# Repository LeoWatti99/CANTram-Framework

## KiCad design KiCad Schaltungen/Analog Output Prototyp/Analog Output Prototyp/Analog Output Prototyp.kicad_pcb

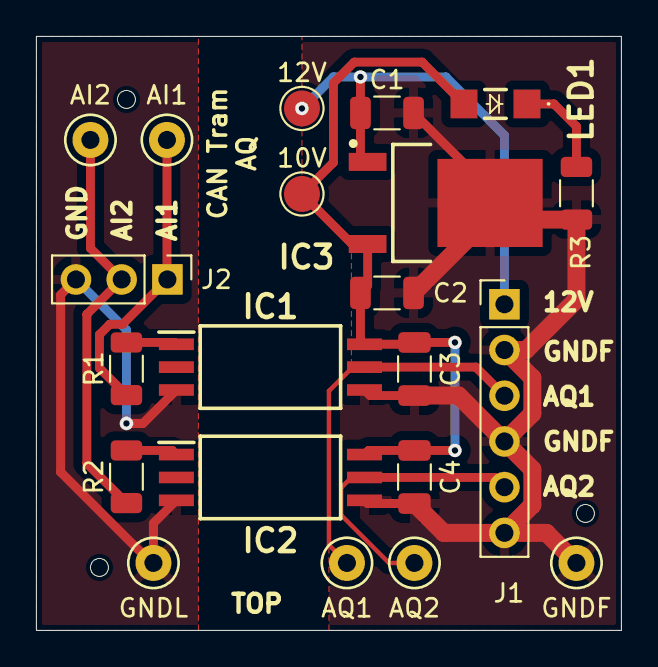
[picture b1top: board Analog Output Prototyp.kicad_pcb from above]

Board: 2 copper layers, 32.5 x 33.0 mm, 21 parts (0 on the bottom side), 11 nets.

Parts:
10V, 12V: TestPoint; TestPoint_Pad_D2.0mm
AI1, AI2: TestPoint_Probe; TestPoint_Keystone_5000-5004_Miniature
AQ1, AQ2: TestPoint_Probe; TestPoint_Keystone_5000-5004_Miniature
C1: 330n; C_1206_3216Metric
C2, C3, C4: 100n; C_1206_3216Metric
GNDF: TestPoint_Probe; TestPoint_Keystone_5000-5004_Miniature
GNDL: TestPoint_Probe; TestPoint_Keystone_5000-5004_Miniature
IC1, IC2: SI8261BAD-C-ISR; SOIC127P1150X265-6N
IC3: L78M10ABDT-TR; TO228P972X240-3N
J1: Conn_01x06; PinHeader_1x06_P2.54mm_Vertical
J2: Conn_01x03; PinHeader_1x03_P2.54mm_Vertical
LED1: 156120GS75000
R1, R2: 100; R_1206_3216Metric
R3: 6,2k; R_1206_3216Metric

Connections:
+10V: 10V.1, C2.1, C3.2, C4.2, IC1.6 (VDD), IC2.6 (VDD), IC3.3 (OUTPUT), LED1.2 (A)
+12V: 12V.1, C1.1, IC3.1 (INPUT), J1.1
GNDF: C1.2, C2.2, C3.1, C4.1, GNDF.1, IC1.4 (GND), IC2.4 (GND), IC3.4 (GND_(TAB)), J1.2, J1.4, J1.6, R3.2
GNDL: GNDL.1, IC1.3 (CATHODE), IC2.3 (CATHODE), J2.3
unnamed: IC1.1 (ANODE), R1.2
unnamed: AQ1.1, IC1.5 (VO), J1.3
unnamed: IC2.1 (ANODE), R2.2
unnamed: AQ2.1, IC2.5 (VO), J1.5
unnamed: AI1.1, J2.1, R1.1
unnamed: AI2.1, J2.2, R2.1
unnamed: LED1.1 (K), R3.1

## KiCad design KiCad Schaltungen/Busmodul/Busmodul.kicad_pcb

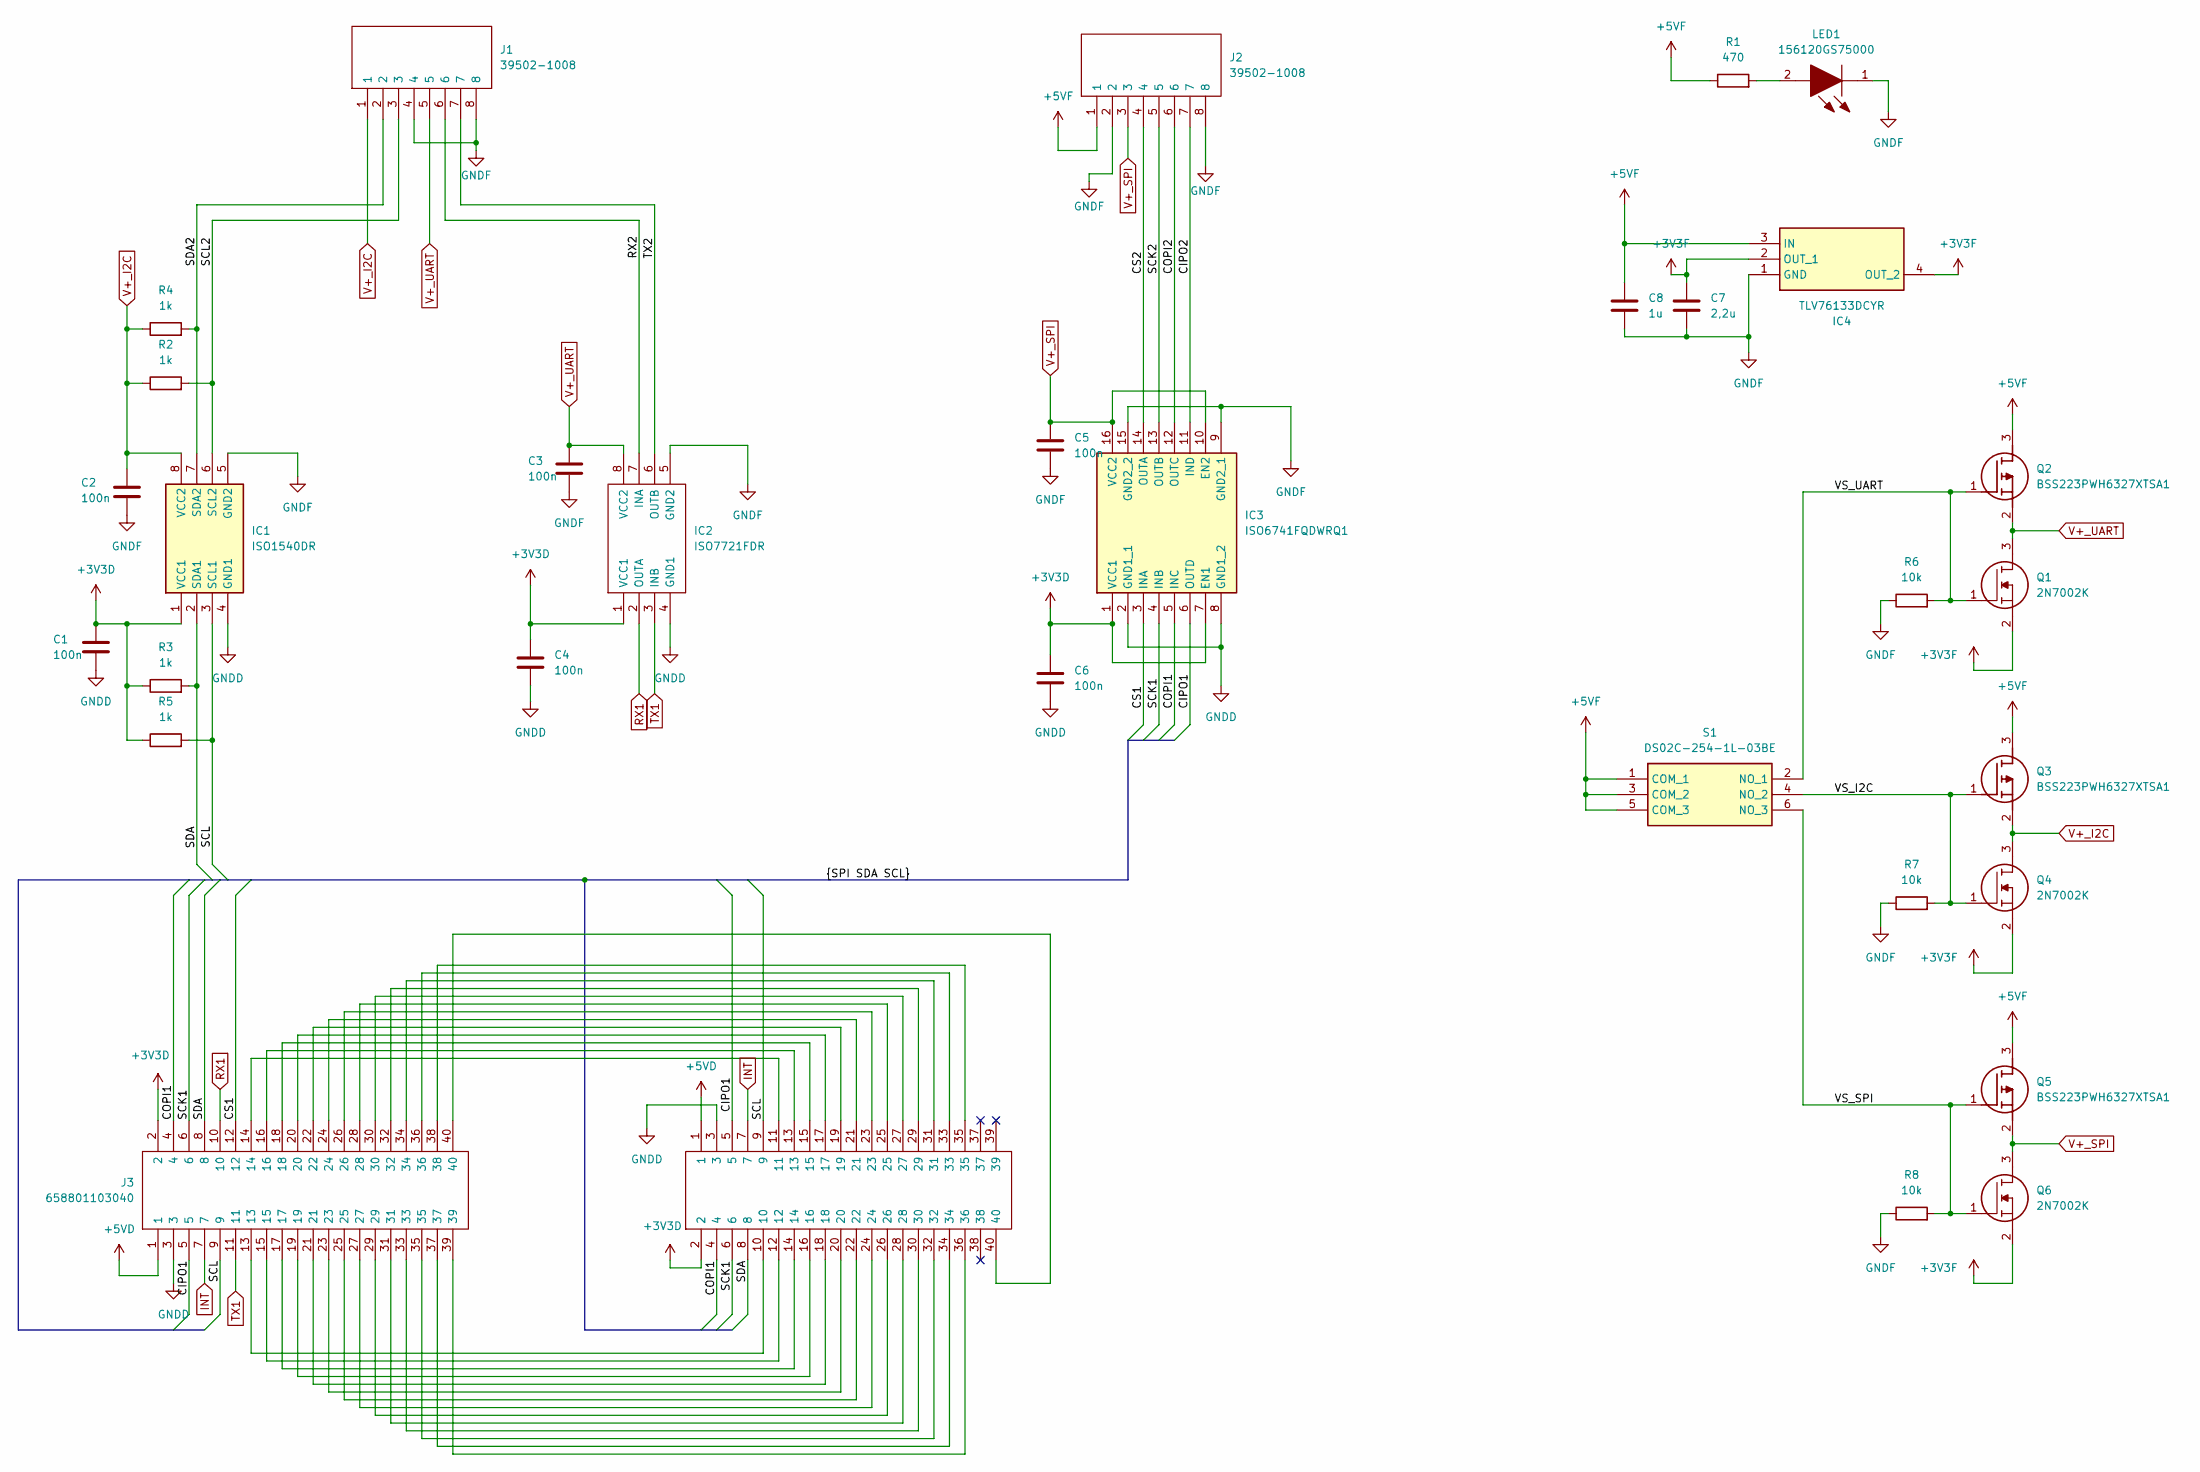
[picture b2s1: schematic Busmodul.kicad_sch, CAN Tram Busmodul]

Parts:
C1, C2, C3, C4, C5, C6: 100n; C_1206_3216Metric
C7: 2,2u; C_1206_3216Metric
C8: 1u; C_1206_3216Metric
IC1: ISO1540DR; SOIC127P600X175-8N; Mouser Part Number 595-ISO1540DR
IC2: ISO7721FDR; SOIC127P600X175-8N; Mouser Part Number 595-ISO7721FDR
IC3: ISO6741FQDWRQ1; SOIC127P1030X265-16N; Mouser Part Number 595-ISO6741FQDWRQ1
IC4: TLV76133DCYR; SOT230P700X180-4N; Mouser Part Number 595-TLV76133DCYR
J1, J2: 39502-1008; SHDRRA8W80P0X350_1X8_2940X920X690P; Mouser Part Number 538-39502-1008
J3: 658801103040; Mouser Part Number 710-658801103040
J4: 658855603040; Mouser Part Number 710-658855603040
LED1: 156120GS75000; Mouser Part Number 710-156120GS75000
Q1, Q4, Q6: 2N7002K; SOT95P240X120-3N; Mouser Part Number 512-2N7002K
Q2, Q3, Q5: BSS223PWH6327XTSA1; SOT65P210X100-3N; Mouser Part Number 726-BSS223PWH6327XTS
R1: 470; R_1206_3216Metric
R2, R3, R4, R5: 1k; R_1206_3216Metric
R6, R7, R8: 10k; R_1206_3216Metric
S1: DS02C-254-1L-03BE; DS02C2541L03BE; Mouser Part Number 490-DS02C-254-1L03BE

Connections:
+3V3D: C1.1, C4.2, C6.1, IC1.1 (VCC1), IC2.1 (VCC1), IC3.1 (VCC1), IC3.7 (EN1), J3.2, J4.2, R3.1, R5.1
+3V3F: C7.1, IC4.2 (OUT_1), IC4.4 (OUT_2), Q1.2, Q4.2, Q6.2
+5VD: J3.1, J4.1
+5VF: C8.1, IC4.3 (IN), J2.1, Q2.3 (D), Q3.3 (D), Q5.3 (D), R1.1, S1.1 (COM_1), S1.3 (COM_2), S1.5 (COM_3)
/CIPO1: IC3.6 (OUTD), J3.5, J4.5
/CIPO2: IC3.11 (IND), J2.7
/COPI1: IC3.5 (INC), J3.4, J4.4
/COPI2: IC3.12 (OUTC), J2.6
/CS1: IC3.3 (INA), J3.12
/CS2: IC3.14 (OUTA), J2.4
/RX2: IC2.7 (INA), J1.6
/SCK1: IC3.4 (INB), J3.6, J4.6
/SCK2: IC3.13 (OUTB), J2.5
/SCL: IC1.3 (SCL1), J3.9, J4.9, R5.2
/SCL2: IC1.6 (SCL2), J1.3, R2.2
/SDA: IC1.2 (SDA1), J3.8, J4.8, R3.2
/SDA2: IC1.7 (SDA2), J1.2, R4.2
/TX2: IC2.6 (OUTB), J1.7
/VS_I2C: Q3.1 (G), Q4.1, R7.2, S1.4 (NO_2)
/VS_SPI: Q5.1 (G), Q6.1, R8.2, S1.6 (NO_3)
/VS_UART: Q1.1, Q2.1 (G), R6.2, S1.2 (NO_1)
GNDD: C1.2, C4.1, C6.2, IC1.4 (GND1), IC2.4 (GND1), IC3.2 (GND1_1), IC3.8 (GND1_2), J3.3, J4.3
GNDF: C2.1, C3.2, C5.1, C7.2, C8.2, IC1.5 (GND2), IC2.5 (GND2), IC3.9 (GND2_1), IC3.15 (GND2_2), IC4.1 (GND), J1.4, J1.8, J2.2, J2.8, LED1.1, R6.1, R7.1, R8.1
INT: J3.7, J4.7
unnamed: J3.13, J4.10
unnamed: J3.14, J4.11
unnamed: J3.15, J4.12
unnamed: J3.16, J4.13
unnamed: J3.17, J4.14
unnamed: J3.18, J4.15
unnamed: J3.19, J4.16
unnamed: J3.20, J4.17
unnamed: J3.21, J4.18
unnamed: J3.22, J4.19
unnamed: J3.23, J4.20
unnamed: J3.24, J4.21
unnamed: J3.25, J4.22
unnamed: J3.26, J4.23
unnamed: J3.27, J4.24
unnamed: J3.28, J4.25
unnamed: J3.29, J4.26
unnamed: J3.30, J4.27
unnamed: J3.31, J4.28
unnamed: J3.32, J4.29
unnamed: J3.33, J4.30
unnamed: J3.34, J4.31
unnamed: J3.35, J4.32
unnamed: J3.36, J4.33
unnamed: J3.37, J4.34
unnamed: J3.38, J4.35
unnamed: J3.39, J4.36
unnamed: J3.40, J4.40
unnamed: LED1.2, R1.2
RX1: IC2.2 (OUTA), J3.10
TX1: IC2.3 (INB), J3.11
V+_I2C: C2.2, IC1.8 (VCC2), J1.1, Q3.2 (S), Q4.3, R2.1, R4.1
V+_SPI: C5.2, IC3.10 (EN2), IC3.16 (VCC2), J2.3, Q5.2 (S), Q6.3
V+_UART: C3.1, IC2.8 (VCC2), J1.5, Q1.3, Q2.2 (S)

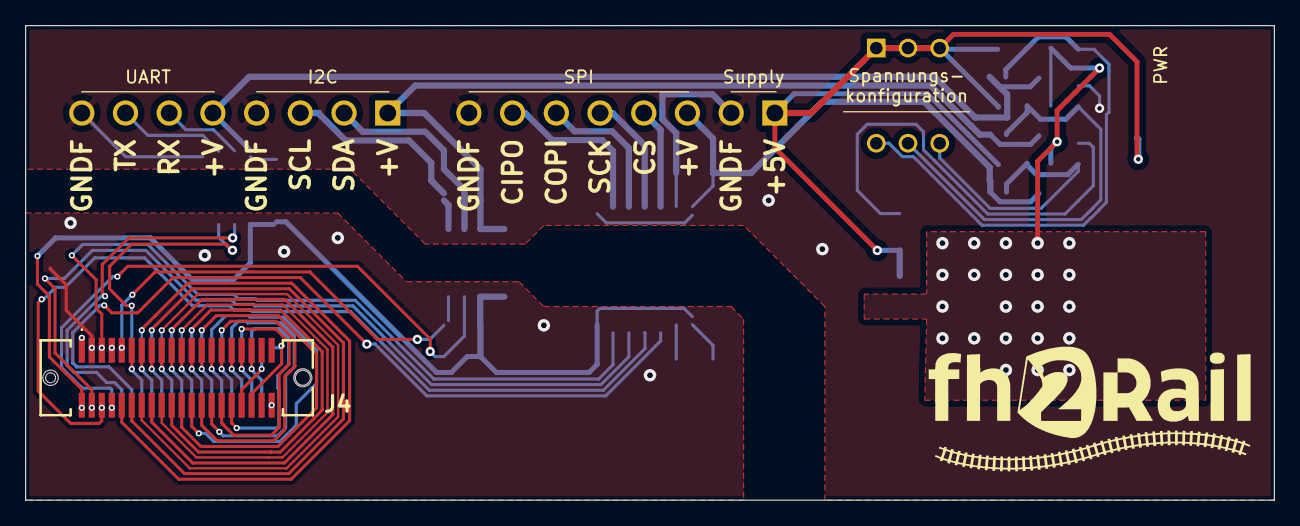
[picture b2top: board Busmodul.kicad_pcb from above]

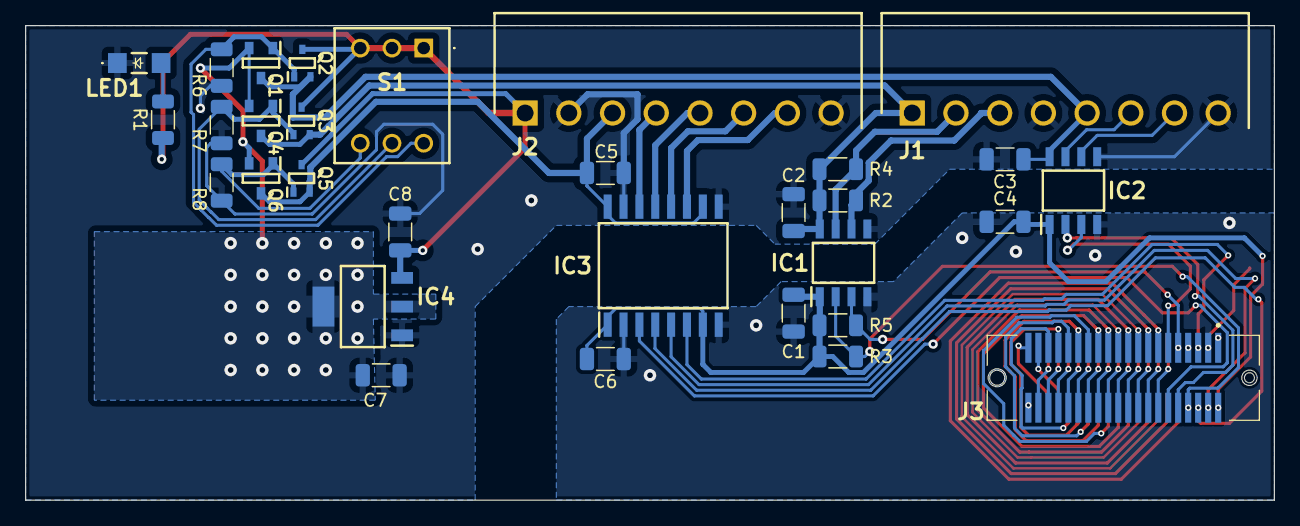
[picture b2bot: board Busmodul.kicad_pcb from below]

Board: 2 copper layers, 100.0 x 38.0 mm, 32 parts (31 on the bottom side), 58 nets.

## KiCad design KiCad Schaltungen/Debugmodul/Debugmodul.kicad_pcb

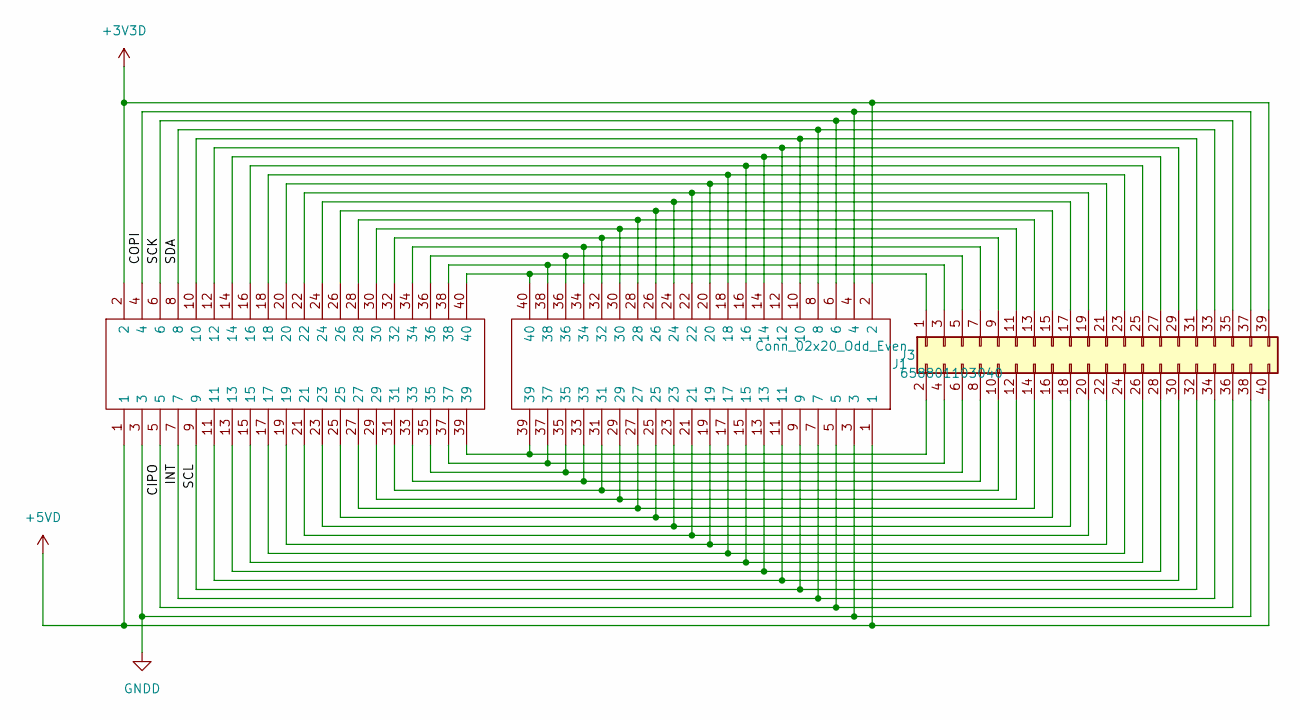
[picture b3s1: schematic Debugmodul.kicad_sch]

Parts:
J1: Conn_02x20_Odd_Even; PinHeader_2x20_P2.54mm_Horizontal
J3: 658801103040; 658855603040; Mouser Part Number 710-658801103040
J4: 658855603040; 658801103040; Mouser Part Number 710-658855603040

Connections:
+3V3D: J1.39, J3.2, J4.2
+5VD: J1.40, J3.1, J4.1
/CIPO: J1.36, J3.5, J4.5
/COPI: J1.37, J3.4, J4.4
/INT: J1.34, J3.7, J4.7
/SCK: J1.35, J3.6, J4.6
/SCL: J1.32, J3.9, J4.9
/SDA: J1.33, J3.8, J4.8
GNDD: J1.38, J3.3, J4.3
unnamed: J1.1, J3.40, J4.40
unnamed: J1.2, J3.39, J4.39
unnamed: J1.3, J3.38, J4.38
unnamed: J1.4, J3.37, J4.37
unnamed: J1.5, J3.36, J4.36
unnamed: J1.6, J3.35, J4.35
unnamed: J1.7, J3.34, J4.34
unnamed: J1.8, J3.33, J4.33
unnamed: J1.9, J3.32, J4.32
unnamed: J1.10, J3.31, J4.31
unnamed: J1.11, J3.30, J4.30
unnamed: J1.12, J3.29, J4.29
unnamed: J1.13, J3.28, J4.28
unnamed: J1.14, J3.27, J4.27
unnamed: J1.15, J3.26, J4.26
unnamed: J1.16, J3.25, J4.25
unnamed: J1.17, J3.24, J4.24
unnamed: J1.18, J3.23, J4.23
unnamed: J1.19, J3.22, J4.22
unnamed: J1.20, J3.21, J4.21
unnamed: J1.21, J3.20, J4.20
unnamed: J1.22, J3.19, J4.19
unnamed: J1.23, J3.18, J4.18
unnamed: J1.24, J3.17, J4.17
unnamed: J1.25, J3.16, J4.16
unnamed: J1.26, J3.15, J4.15
unnamed: J1.27, J3.14, J4.14
unnamed: J1.28, J3.13, J4.13
unnamed: J1.29, J3.12, J4.12
unnamed: J1.30, J3.11, J4.11
unnamed: J1.31, J3.10, J4.10

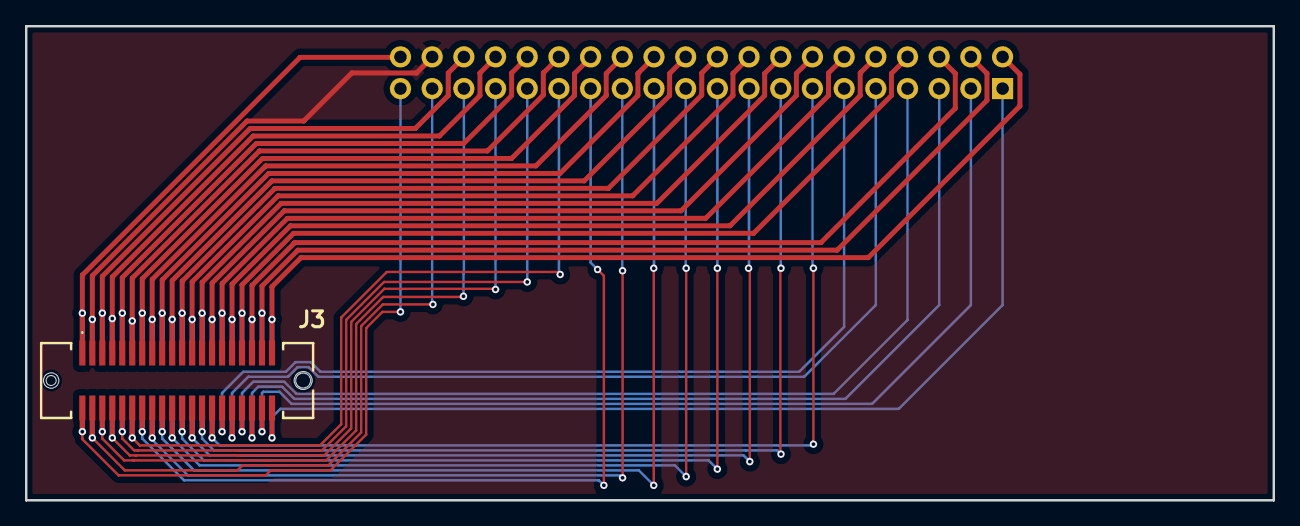
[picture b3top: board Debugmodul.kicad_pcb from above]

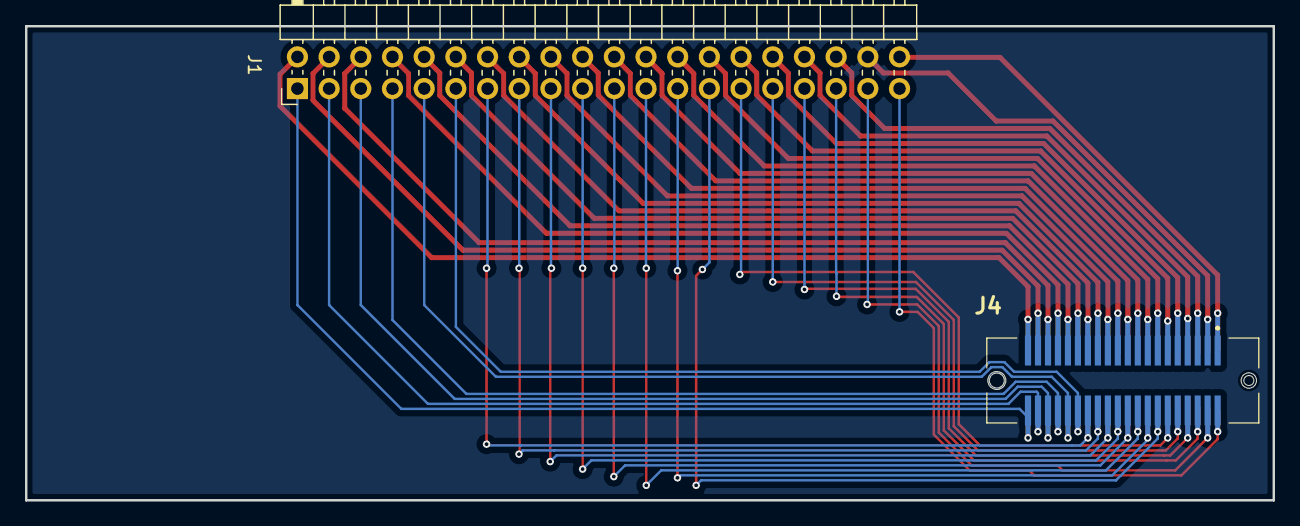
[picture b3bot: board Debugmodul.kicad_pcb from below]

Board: 2 copper layers, 100.0 x 38.0 mm, 3 parts (2 on the bottom side), 40 nets.

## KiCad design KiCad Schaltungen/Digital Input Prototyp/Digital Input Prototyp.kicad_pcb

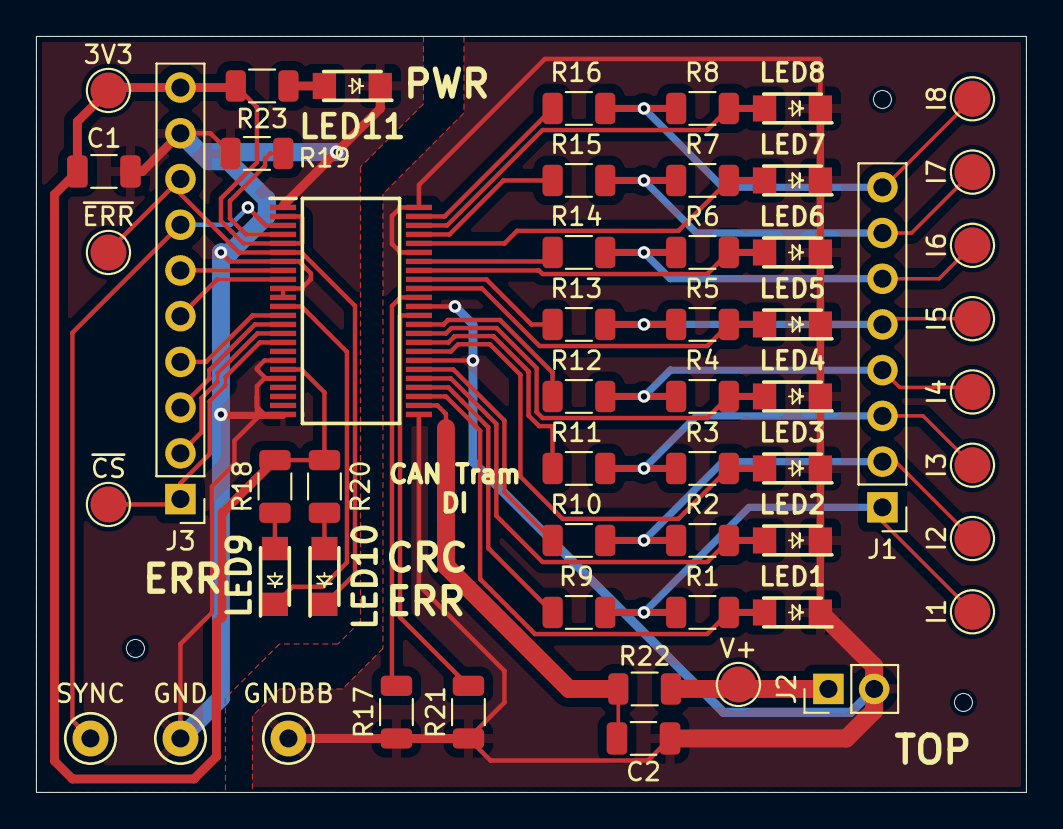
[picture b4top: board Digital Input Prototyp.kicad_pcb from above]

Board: 2 copper layers, 55.0 x 42.0 mm, 53 parts (0 on the bottom side), 44 nets.

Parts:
3V3: TestPoint; TestPoint_Pad_D2.0mm
C1: 100n; C_1206_3216Metric
C2: 330n; C_1206_3216Metric
GND: TestPoint_Probe; TestPoint_Keystone_5000-5004_Miniature
GNDBB: TestPoint_Probe; TestPoint_Keystone_5000-5004_Miniature
I1, I2, I3, I4, I5, I6, I7, I8: TestPoint; TestPoint_Pad_D2.0mm
IC1: ISO1I813T; SOP50P810X110-48N
J1: Conn_01x08_Socket; PinHeader_1x08_P2.54mm_Vertical
J2: Conn_01x02; PinHeader_1x02_P2.54mm_Vertical
J3: Conn_01x10; PinHeader_1x10_P2.54mm_Vertical
LED1, LED2, LED3, LED4, LED5, LED6, LED7, LED8: 156120YS75000; LEDM3216X130N
LED9, LED10: 156120RS75000; LEDM3216X130N
LED11: 156120GS75000; LEDM3216X130N
R1, R2, R3, R4, R5, R6, R7, R8: 12k; R_1206_3216Metric
R9, R10, R11, R12, R13, R14, R15, R16: 2k; R_1206_3216Metric
R17: 40k; R_1206_3216Metric
R18, R20: 470; R_1206_3216Metric
R19, R23: 22k; R_1206_3216Metric
R21: 330k; R_1206_3216Metric
R22: 100; R_1206_3216Metric
SYNC: TestPoint_Probe; TestPoint_Keystone_5000-5004_Miniature
V+: TestPoint; TestPoint_Pad_D2.0mm

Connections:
+3V3: 3V3.1, C1.1, IC1.2 (SEL), IC1.5 (VCC), IC1.19 (MS0), J3.10, R18.2, R20.2, R23.2
/I1: I1.1, J1.1, R1.1, R9.1
/I2: I2.1, J1.2, R2.1, R10.1
/I3: I3.1, J1.3, R3.1, R11.1
/I4: I4.1, J1.4, R4.1, R12.1
/I5: I5.1, J1.5, R5.1, R13.1
/I6: I6.1, J1.6, R6.1, R14.1
/I7: I7.1, J1.7, R7.1, R15.1
/I8: I8.1, J1.8, R8.1, R16.1
/IH1: IC1.28 (I0H), R9.2
/IH2: IC1.30 (I1H), R10.2
/IH3: IC1.33 (I2H), R11.2
/IH4: IC1.35 (I3H), R12.2
/IH5: IC1.40 (I4H), R13.2
/IH6: IC1.42 (I5H), R14.2
/IH7: IC1.45 (I6H), R15.2
/IH8: IC1.47 (I7H), R16.2
/IL1: IC1.27 (I0L), LED1.2 (A), R1.2
/IL2: IC1.29 (I1L), LED2.2 (A), R2.2
/IL3: IC1.32 (I2L), LED3.2 (A), R3.2
/IL4: IC1.34 (I3L), LED4.2 (A), R4.2
/IL5: IC1.39 (I4L), LED5.2 (A), R5.2
/IL6: IC1.41 (I5L), LED6.2 (A), R6.2
/IL7: IC1.44 (I6L), LED7.2 (A), R7.2
/IL8: IC1.46 (I7L), LED8.2 (A), R8.2
/SCLK: IC1.13 (SCLK), J3.4
/SDI: IC1.8 (SDI), J3.6
/SDO: IC1.15 (SDO), J3.2
/SSI: IC1.14 (SSI), J3.3
/SSO: IC1.9 (SSO), J3.5
/SYNC: IC1.3 (SYNC), J3.7, SYNC.1
/~CS: IC1.16 (~CS), J3.1
/~ERR: IC1.6 (~ERR), J3.8, LED10.1 (K)
GND: C1.2, GND.1, IC1.1 (GND_1), IC1.7 (GND_2), IC1.10 (GND), IC1.11 (GND), IC1.18 (GND_3), IC1.20 (MS1), IC1.24 (GND_4), J3.9, LED11.1 (K), R19.2
GNDBB: C2.1, GNDBB.1, IC1.25 (GNDBB_1), IC1.31 (GNDBB_2), IC1.37 (GNDBB_3), IC1.43 (GNDBB_4), IC1.48 (GNDBB_5), J2.2, LED1.1 (K), LED2.1 (K), LED3.1 (K), LED4.1 (K), LED5.1 (K), LED6.1 (K), LED7.1 (K), LED8.1 (K), R17.1, R21.1
unnamed: IC1.4 (ROSC), R19.1
unnamed: IC1.36 (TS), R21.2
unnamed: C2.2, IC1.26 (VBB), R22.1
unnamed: IC1.38 (WB), R17.2
unnamed: IC1.12 (~CRCERR), LED9.1 (K)
unnamed: J2.1, R22.2, V+.1
unnamed: LED9.2 (A), R18.1
unnamed: LED10.2 (A), R20.1
unnamed: LED11.2 (A), R23.1

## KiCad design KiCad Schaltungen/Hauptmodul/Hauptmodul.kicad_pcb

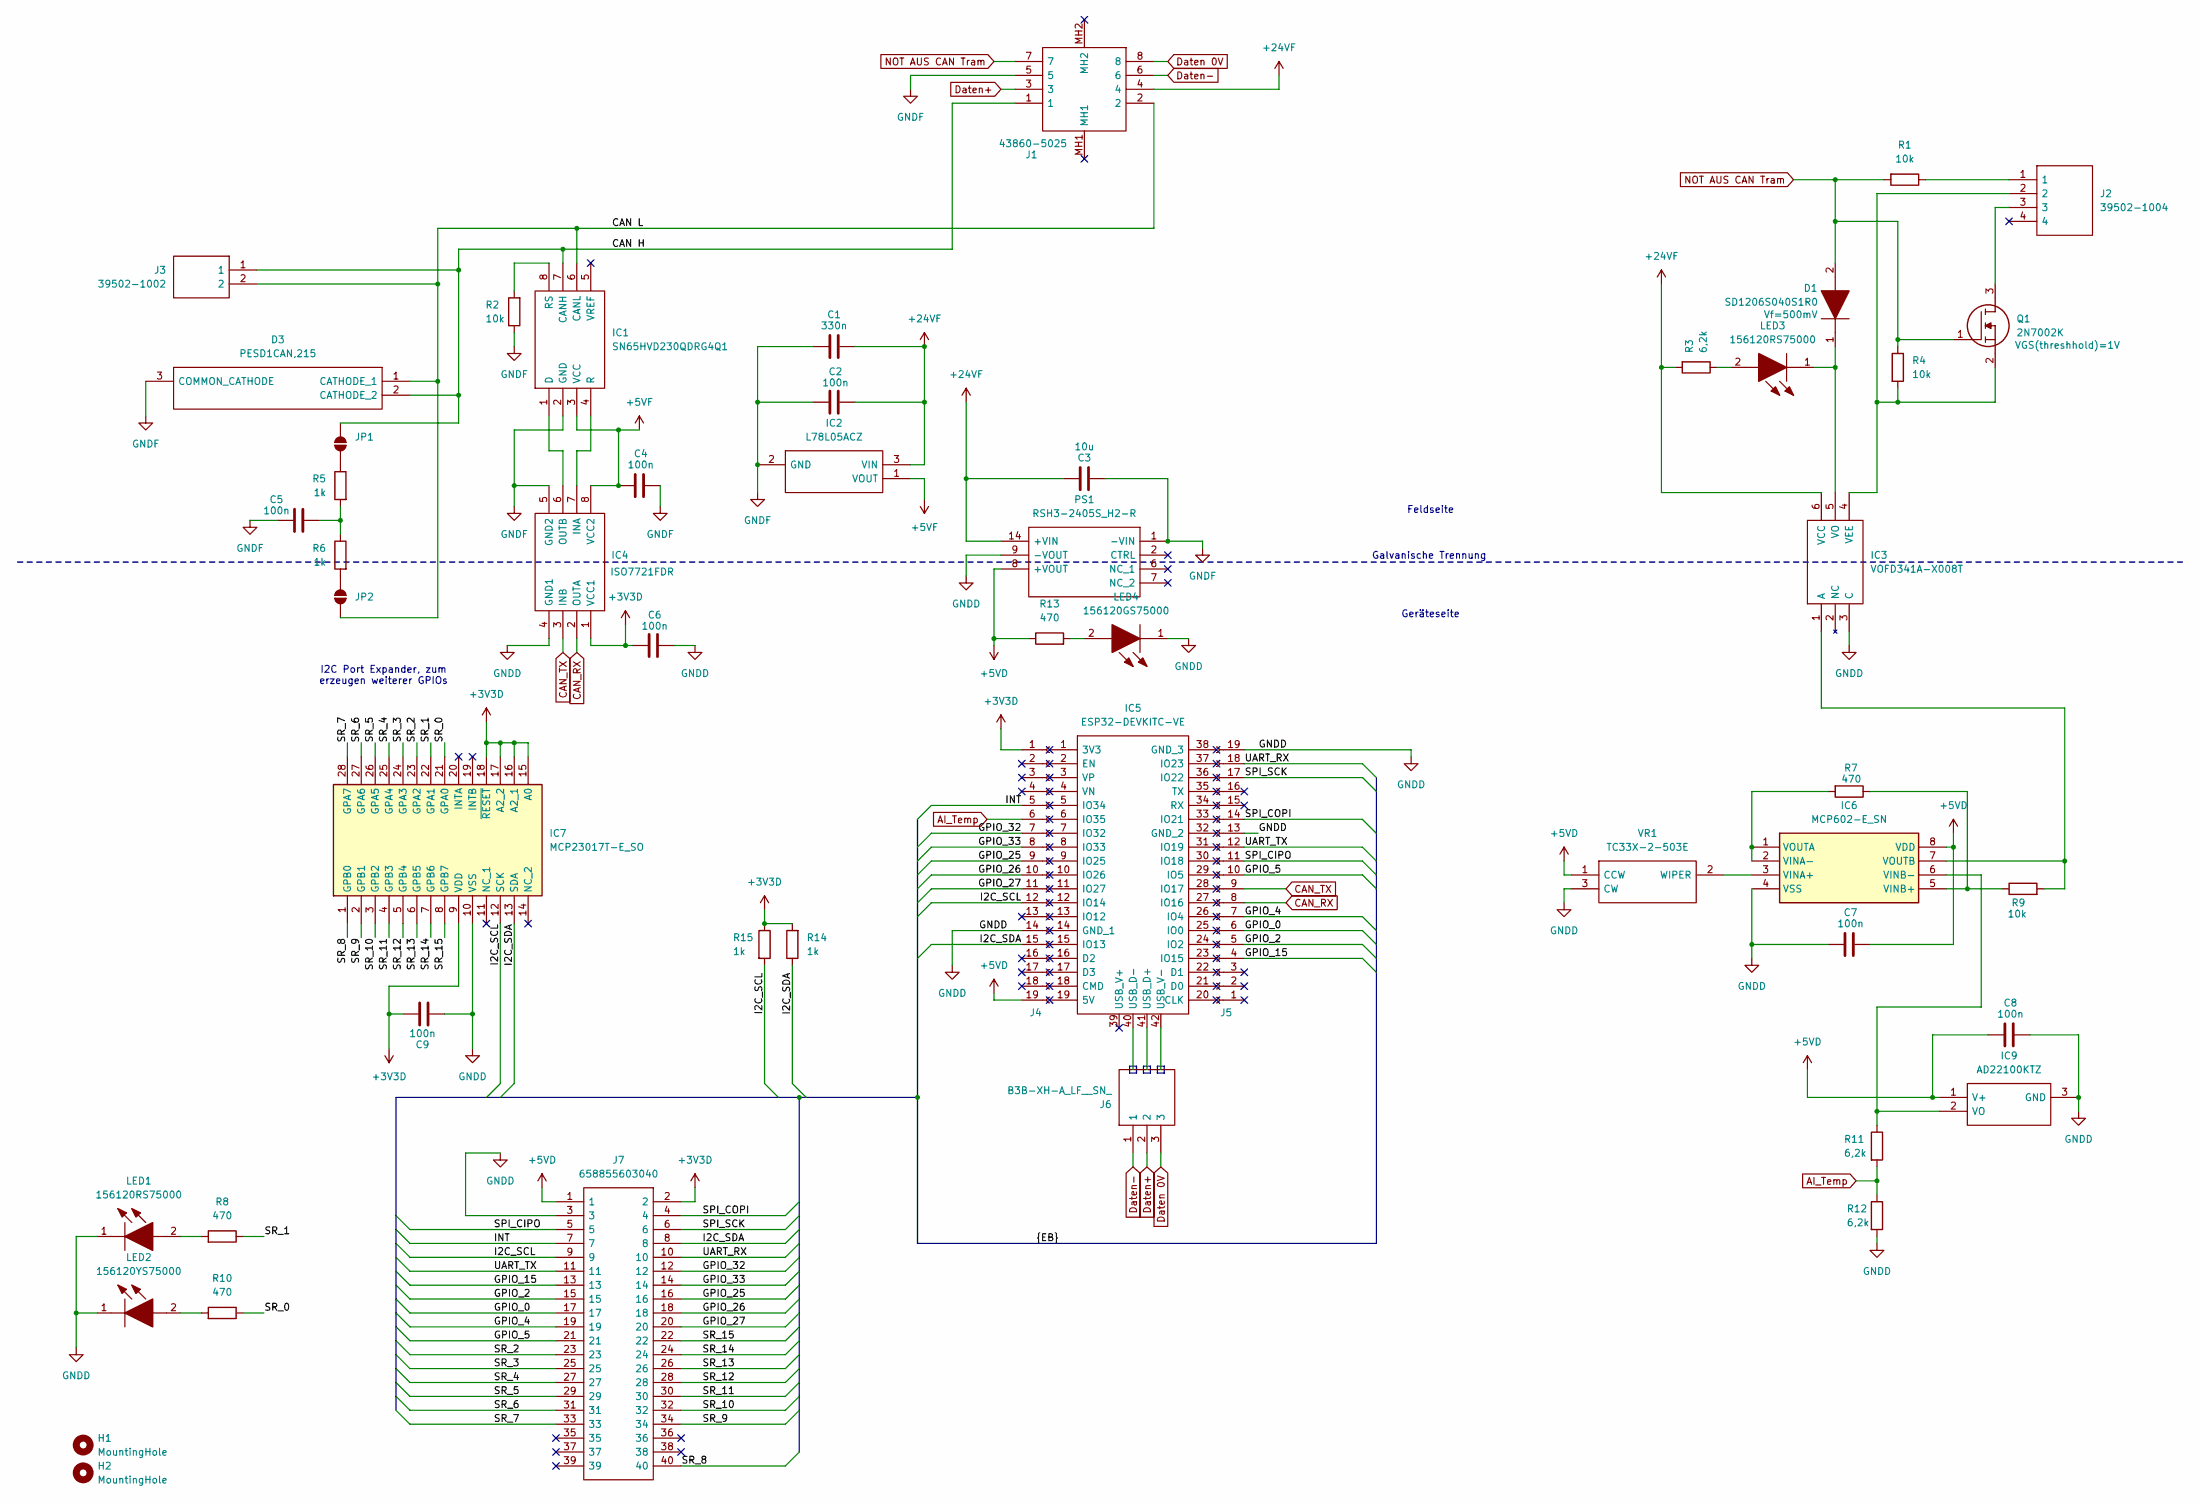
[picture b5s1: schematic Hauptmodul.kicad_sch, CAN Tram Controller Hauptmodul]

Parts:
C1: 330n; C_1206_3216Metric; Manufacturer_Part_Number CL31A106KBHNNNE; Mouser Part Number 187-CL31A106KBHNNNE
C2, C4, C5, C6, C7, C8, C9: 100n; C_1206_3216Metric; Manufacturer_Part_Number CL31A106KBHNNNE; Mouser Part Number 187-CL31A106KBHNNNE
C3: 10u; C_1206_3216Metric; Manufacturer_Part_Number CL31A106KBHNNNE; Mouser Part Number 187-CL31A106KBHNNNE
D1: SD1206S040S1R0; DIOC3419X116N; Mouser Part Number 581-SD1206S040S1R0
D3: PESD1CAN,215; SOT95P230X110-3N; Mouser Part Number 771-PESD1CAN-T/R
H1, H2: MountingHole; MountingHole_3.2mm_M3
IC1: SN65HVD230QDRG4Q1; SOIC127P600X175-8N; Mouser Part Number 595-S65HVD230QDRG4Q1
IC2: L78L05ACZ; Mouser Part Number 511-L78L05ACZ
IC3: VOFD341A-X008T; SOIC127P1150X378-6N; Mouser Part Number 625-VOFD341A-X008T
IC4: ISO7721FDR; SOIC127P600X175-8N; Mouser Part Number 595-ISO7721FDR
IC5: ESP32-DEVKITC-VE; ESP32DEVKITCVE; Manufacturer_Part_Number ESP32-DEVKITC-VE; Mouser Part Number 356-ESP32-DEVKTC32VE
IC6: MCP602-E_SN; SOIC127P600X175-8N; Mouser Part Number 579-MCP602-E/SN
IC7: MCP23017T-E_SO; SOIC127P1030X265-28N; Mouser Part Number 579-MCP23017T-E/SO
IC9: AD22100KTZ; TO128P419X483X533-3P; Mouser Part Number 584-AD22100KTZ
J1: 43860-5025; 438605025; Mouser Part Number 538-43860-5025
J2: 39502-1004; SHDRRA4W80P0X350_1X4_1540X920X730P; Mouser Part Number 538-39502-1004
J3: 39502-1002; SHDR2W80P0X350_1X2_840X920X690P; Mouser Part Number 538-39502-1002
J4, J5: Conn_01x19_Socket; PinSocket_1x19_P2.54mm_Vertical
J6: B3B-XH-A_LF__SN_; B3BXHALFSN; Mouser Part Number 306-B3BXHALFSNP
J7: 658855603040; Mouser Part Number 710-658855603040
JP1, JP2: SolderJumper_2_Open; SolderJumper-2_P1.3mm_Open_Pad1.0x1.5mm
LED1, LED3: 156120RS75000; LEDM3216X130N; Mouser Part Number 710-156120RS75000
LED2: 156120YS75000; LEDC5017X140N; Mouser Part Number 710-156120YS75000
LED4: 156120GS75000; Mouser Part Number 710-156120GS75000
PS1: RSH3-2405S_H2-R; RSH32405SH2R; Mouser Part Number 919-RSH3-2405S/H2-R
Q1: 2N7002K; SOT95P240X120-3N; Mouser Part Number 512-2N7002K
R1, R4: 10k; R_1206_3216Metric; Manufacturer_Part_Number AC1206FR-076K2L; Mouser Part Number 603-AC1206FR-076K2L
R2: 10k; R_1206_3216Metric; Manufacturer_Part_Number RC1206FR-1310KL; Mouser Part Number 603-RC1206FR-1310KL
R3, R11: 6,2k; R_1206_3216Metric; Manufacturer_Part_Number AC1206FR-076K2L; Mouser Part Number 603-AC1206FR-076K2L
R5, R6: 1k; R_1206_3216Metric
R7: 470; R_1206_3216Metric; Manufacturer_Part_Number RC1206FR-0712KL; Mouser Part Number 603-RC1206FR-0712KL
R8, R10: 470; R_1206_3216Metric
R9: 10k; R_1206_3216Metric; Manufacturer_Part_Number RC1206FR-0712KL; Mouser Part Number 603-RC1206FR-0712KL
R12: 6,2k; R_1206_3216Metric; Manufacturer_Part_Number RC1206FR-0712KL; Mouser Part Number 603-RC1206FR-0712KL
R13: 470; R_1206_3216Metric; Manufacturer_Part_Number AC1206FR-076K2L; Mouser Part Number 603-AC1206FR-076K2L
R14, R15: 1k; R_1206_3216Metric; Manufacturer_Part_Number AC1206FR-076K2L; Mouser Part Number 603-AC1206FR-076K2L
VR1: TC33X-2-503E; TC33X2503E; Mouser Part Number 652-TC33X-2-503E

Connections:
+3V3D: C6.2, C9.2, IC4.1 (VCC1), IC7.9 (VDD), IC7.15 (A0), IC7.16 (A2_1), IC7.17 (A2_2), IC7.18 (~RESET), J4.1, J7.2, R14.2, R15.1
+5VD: C7.1, C8.2, IC6.8 (VDD), IC9.1 (V+), J4.19, J7.1, PS1.8 (+VOUT), R13.1, VR1.1 (CCW)
+5VF: C4.2, IC1.3 (VCC), IC2.1 (VOUT), IC4.8 (VCC2)
+24VF: C1.2, C2.2, C3.1, IC2.3 (VIN), IC3.6 (VCC), J1.4, PS1.14 (+VIN), R3.2
/CAN H: D3.2 (CATHODE_2), IC1.7 (CANH), J1.1, J3.1, JP1.2 (B)
/CAN L: D3.1 (CATHODE_1), IC1.6 (CANL), J1.2, J3.2, JP2.2 (B)
/GPIO_0: J5.6, J7.17
/GPIO_2: J5.5, J7.15
/GPIO_4: J5.7, J7.19
/GPIO_5: J5.10, J7.21
/GPIO_15: J5.4, J7.13
/GPIO_25: J4.9, J7.16
/GPIO_26: J4.10, J7.18
/GPIO_27: J4.11, J7.20
/GPIO_32: J4.7, J7.12
/GPIO_33: J4.8, J7.14
/I2C_SCL: IC7.12 (SCK), J4.12, J7.9, R15.2
/I2C_SDA: IC7.13 (SDA), J4.15, J7.8, R14.1
/INT: J4.5, J7.7
/SPI_CIPO: J5.11, J7.5
/SPI_COPI: J5.14, J7.4
/SPI_SCK: J5.17, J7.6
/SR_0: IC7.21 (GPA0), R10.1
/SR_1: IC7.22 (GPA1), R8.1
/SR_2: IC7.23 (GPA2), J7.23
/SR_3: IC7.24 (GPA3), J7.25
/SR_4: IC7.25 (GPA4), J7.27
/SR_5: IC7.26 (GPA5), J7.29
/SR_6: IC7.27 (GPA6), J7.31
/SR_7: IC7.28 (GPA7), J7.33
/SR_8: IC7.1 (GPB0), J7.40
/SR_9: IC7.2 (GPB1), J7.34
/SR_10: IC7.3 (GPB2), J7.32
/SR_11: IC7.4 (GPB3), J7.30
/SR_12: IC7.5 (GPB4), J7.28
/SR_13: IC7.6 (GPB5), J7.26
/SR_14: IC7.7 (GPB6), J7.24
/SR_15: IC7.8 (GPB7), J7.22
/UART_RX: J5.18, J7.10
/UART_TX: J5.12, J7.11
AI_Temp: J4.6, R11.2, R12.1
CAN_RX: IC4.2 (OUTA), J5.8
CAN_TX: IC4.3 (INB), J5.9
Daten 0V: J1.8, J6.3
Daten+: J1.3, J6.2
Daten-: J1.6, J6.1
GNDD: C6.1, C7.2, C8.1, C9.1, IC3.3 (C), IC4.4 (GND1), IC6.4 (VSS), IC7.10 (VSS), IC9.3 (GND), J4.14, J5.13, J5.19, J7.3, LED1.1, LED2.1, LED4.1, PS1.9 (-VOUT), R12.2, VR1.3 (CW)
GNDF: C1.1, C2.1, C3.2, C4.1, C5.2, D3.3 (COMMON_CATHODE), IC1.2 (GND), IC2.2 (GND), IC4.5 (GND2), J1.5, PS1.1 (-VIN), R2.1
NOT AUS CAN Tram: D1.2, J1.7, Q1.1, R1.2, R4.1
unnamed: C5.1, R5.2, R6.1
unnamed: IC1.1 (D), IC4.6 (OUTB)
unnamed: IC1.4 (R), IC4.7 (INA)
unnamed: IC1.8 (RS), R2.2
unnamed: IC3.1 (A), IC6.7 (VOUTB), R9.2
unnamed: IC3.4 (VEE), J2.2, Q1.2, R4.2
unnamed: D1.1, IC3.5 (VO), LED3.1
unnamed: IC6.3 (VINA+), VR1.2 (WIPER)
unnamed: IC6.1 (VOUTA), IC6.2 (VINA-), R7.2
unnamed: IC6.5 (VINB+), R7.1, R9.1
unnamed: IC6.6 (VINB-), IC9.2 (VO), R11.1
unnamed: J2.1, R1.1
unnamed: J2.3, Q1.3
unnamed: JP1.1 (A), R5.1
unnamed: JP2.1 (A), R6.2
unnamed: LED1.2, R8.2
unnamed: LED2.2, R10.2
unnamed: LED3.2, R3.1
unnamed: LED4.2, R13.2

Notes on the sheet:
Galvanische Trennung
Geräteseite
Feldseite
I2C Port Expander, zum erzeugen weiterer GPIOs

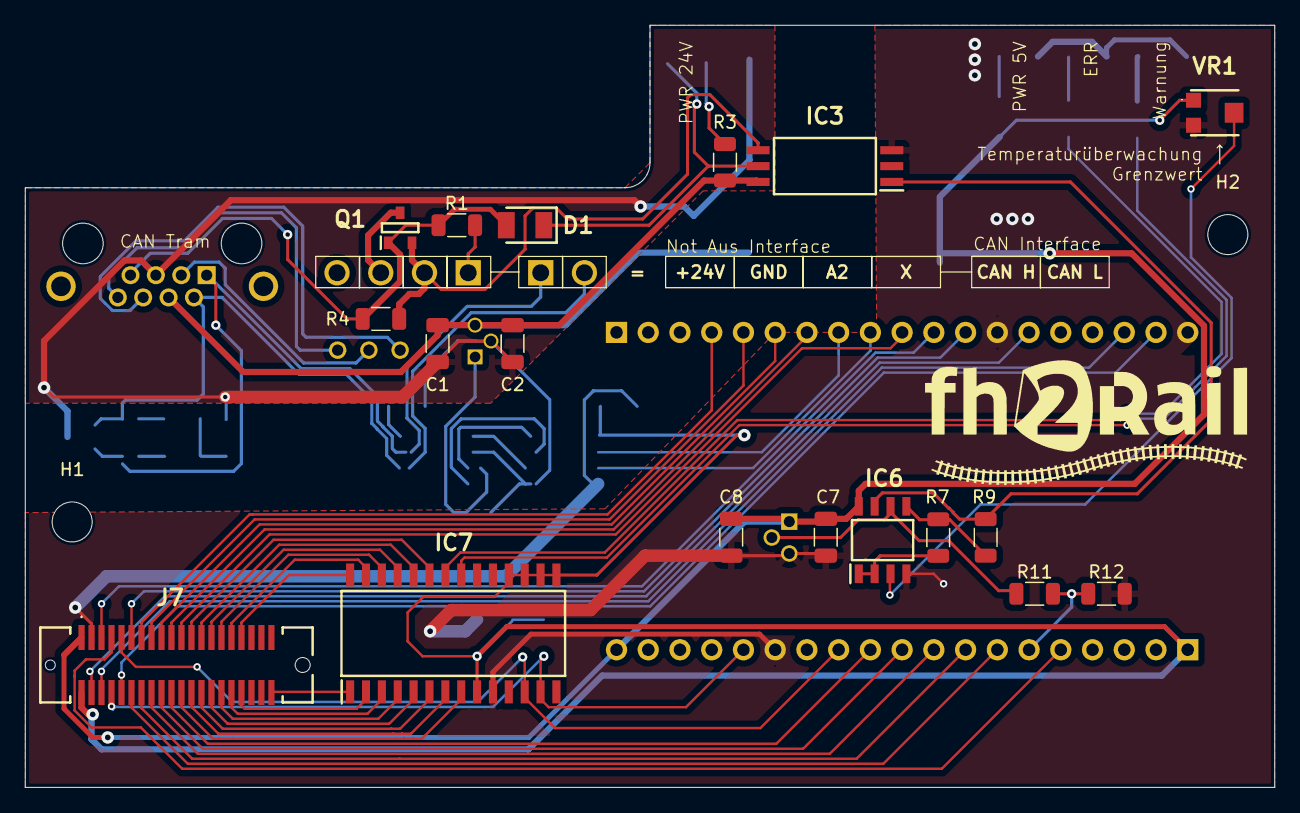
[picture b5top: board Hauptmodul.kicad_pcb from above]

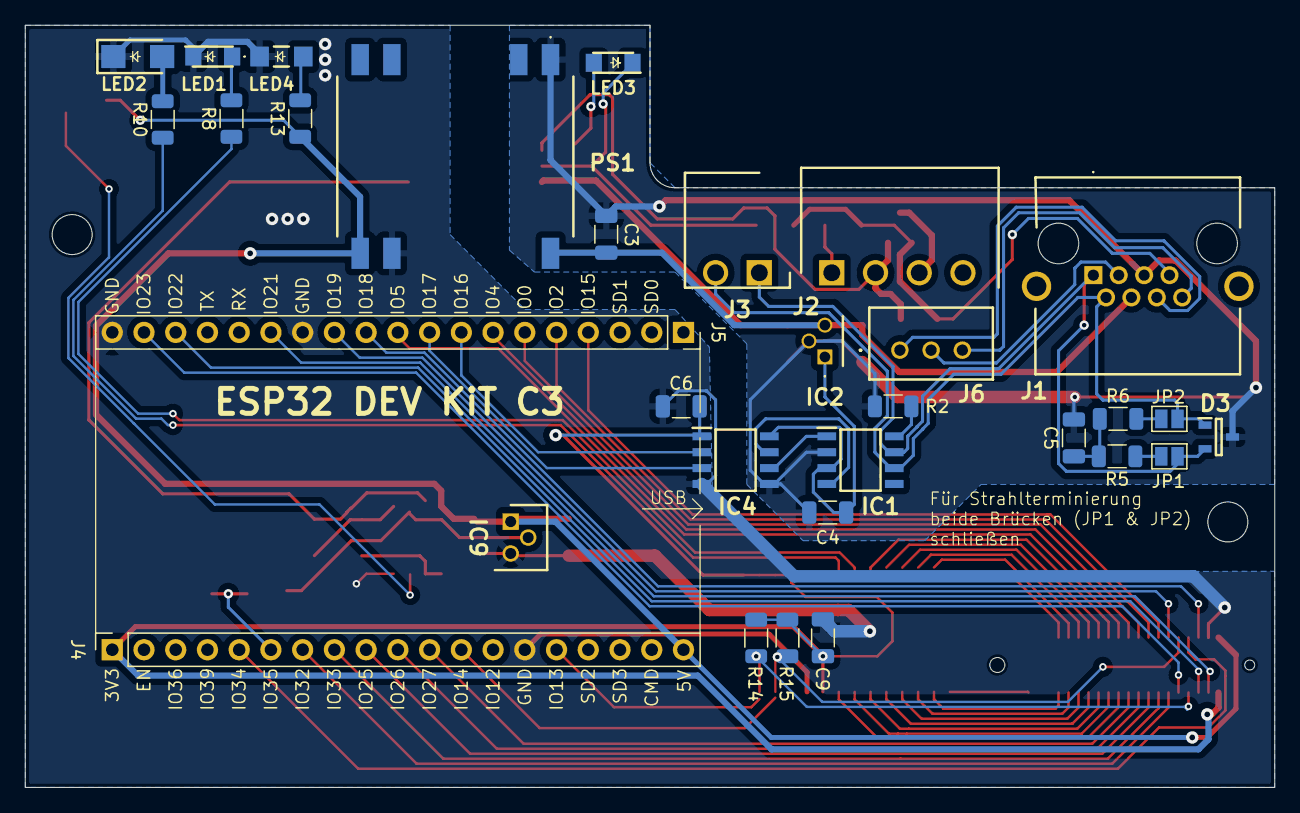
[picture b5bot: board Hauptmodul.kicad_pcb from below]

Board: 2 copper layers, 100.0 x 61.0 mm, 51 parts (31 on the bottom side), 68 nets.
